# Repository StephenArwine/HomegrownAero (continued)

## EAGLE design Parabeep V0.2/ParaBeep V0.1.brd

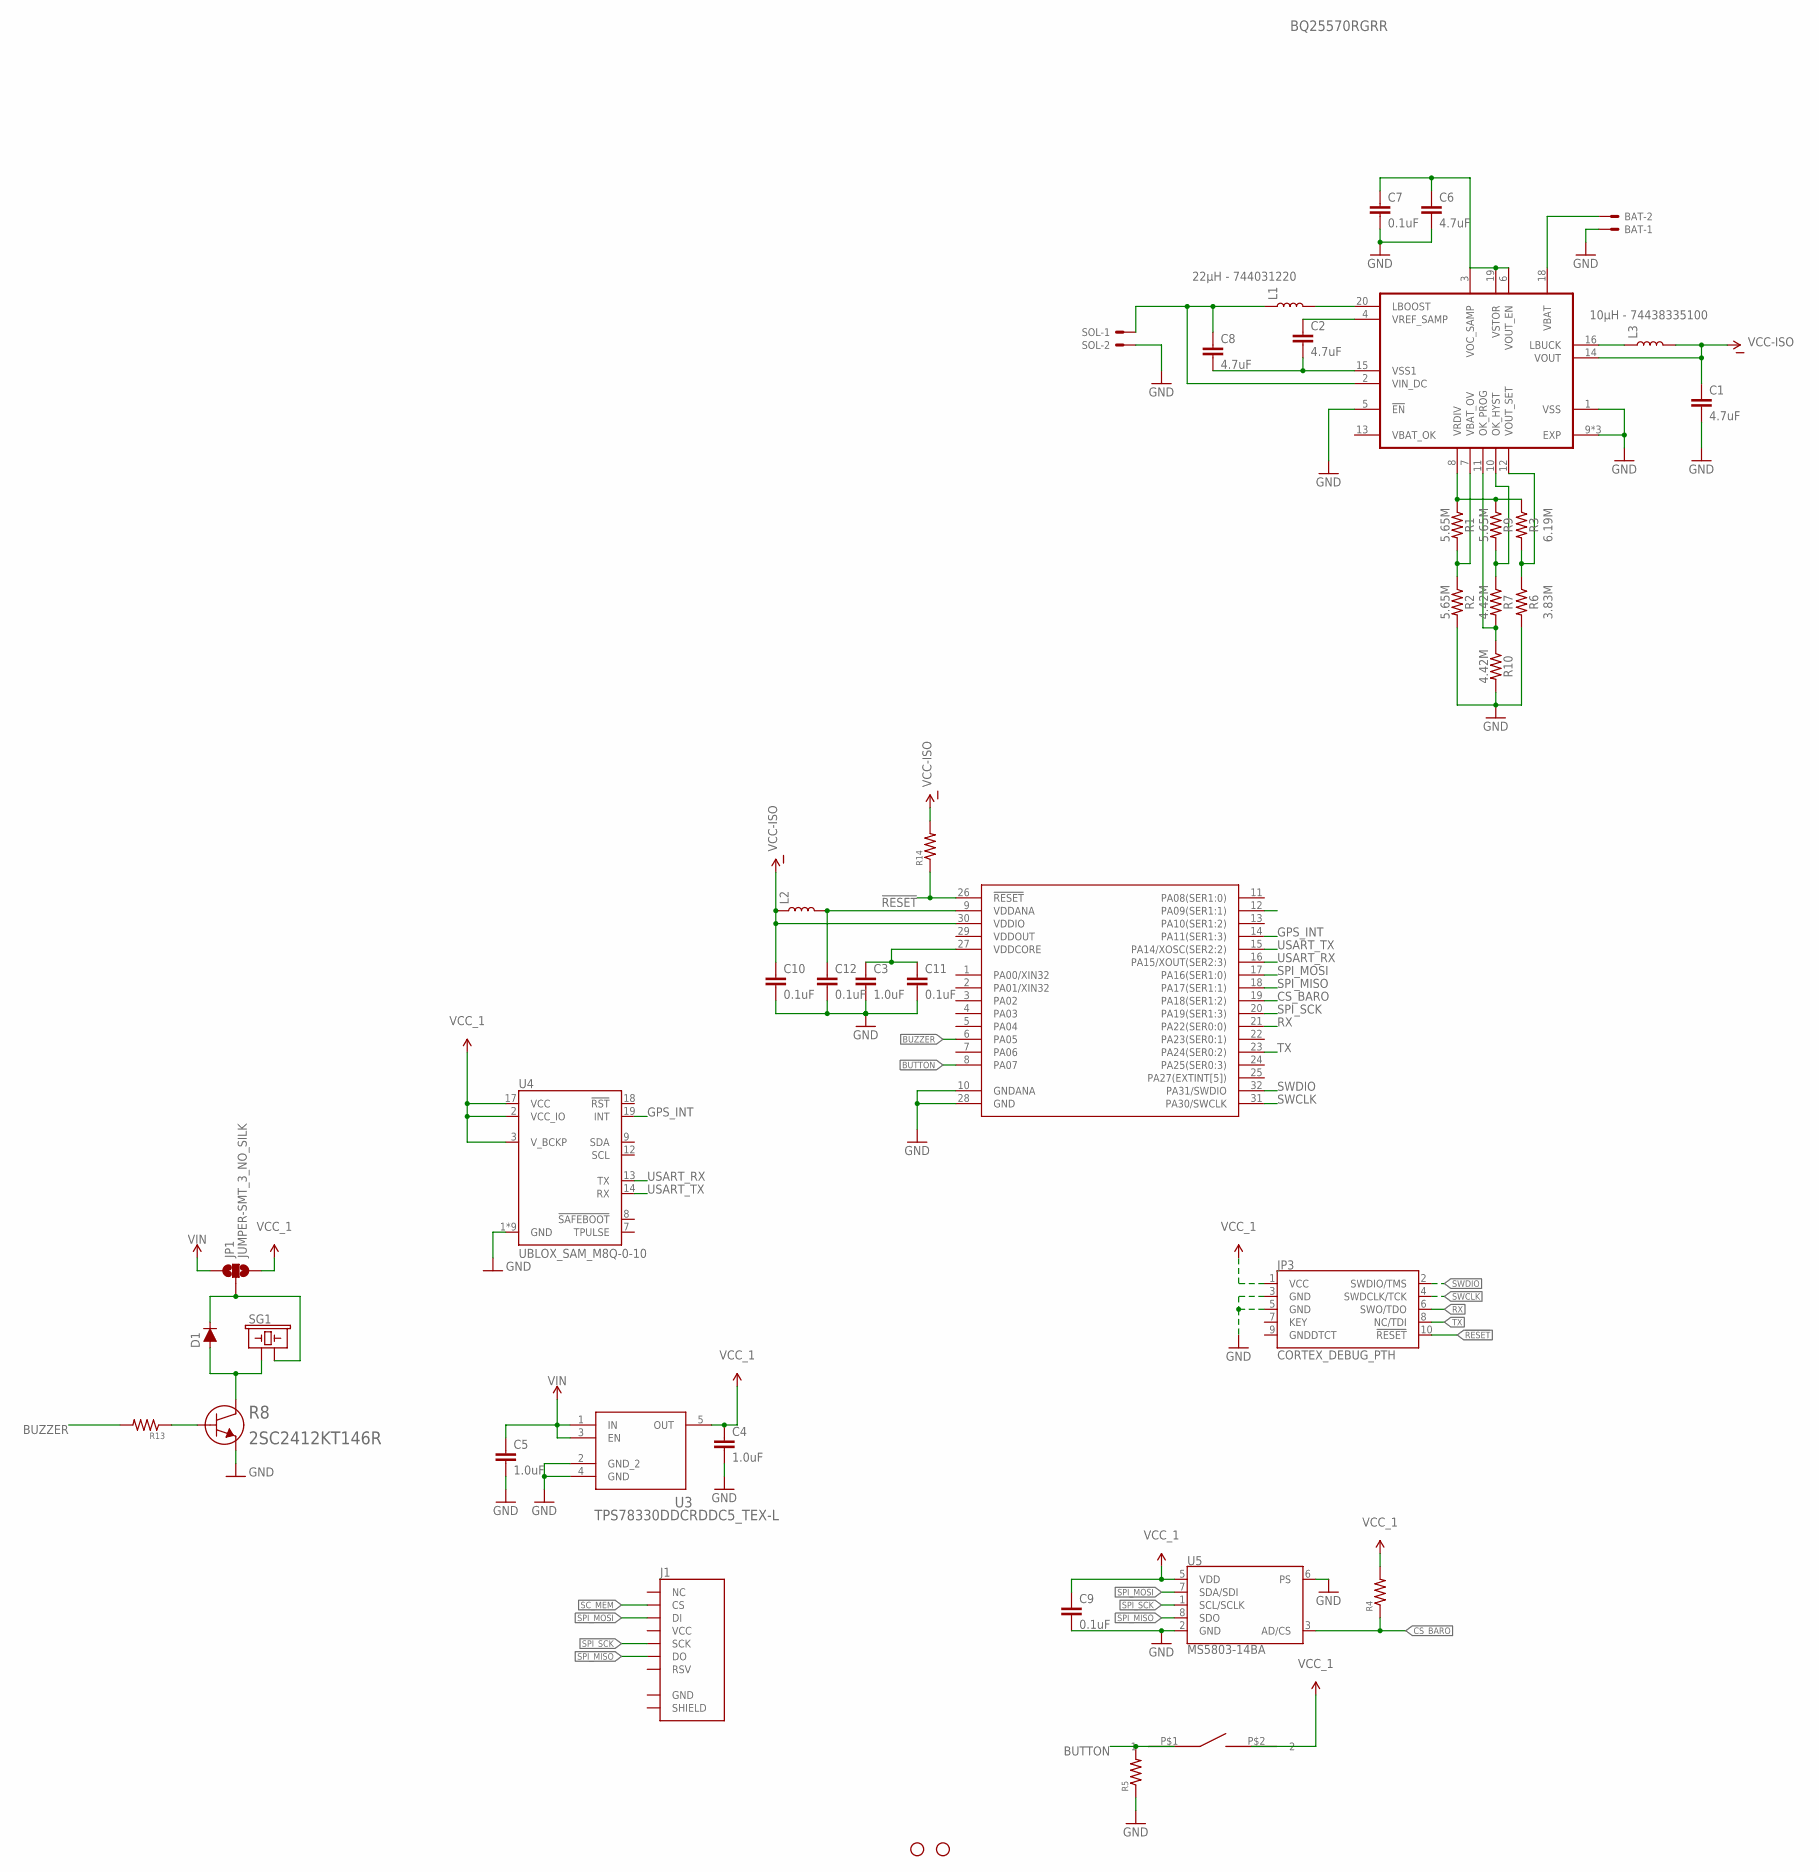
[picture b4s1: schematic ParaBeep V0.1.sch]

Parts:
BAT: SM02B-SSR-H-TB
C1, C2, C6, C8: 4.7uF; 0603
C3, C4, C5: 1.0uF; 0603
C7, C9, C10, C11, C12: 0.1uF; 0603
D1: 250mA/100V; SOD-323
H1, H2: STAND-OFFTIGHT; STAND-OFF-TIGHT
J1: MICRO-SD_CARD_SOCKETPUSH-PUSH; MICRO-SD-SOCKET
JP1: JUMPER-SMT_3_NO_SILK; SMT-JUMPER_3_NO_SILK
JP3: CORTEX_DEBUG_PTH; 2X5-PTH-1.27MM
L1: 22µH - 744031220; INDUCTOR_4.7UH
L2: INDUCTORFB-30OHM; 0603
L3: 10µH - 74438335100; INDUCTOR_4.7UH
R1, R2, R9: 5.65M; 0603
R3: 6.19M; 0603
R4, R5, R13, R14: 0402
R6: 3.83M; 0603
R7, R10: 4.42M; 0603
R8: 2SC2412KT146R; TRANS_2SB852K_ROM
SG1: BUZZER-SMD_KIT; BUZZER-CCV-KIT
SOL: SM02B-SSR-H-TB
U2: BQ25570RGRR; QFN50P350X350X100-21N
U3: TPS78330DDCRDDC5_TEX-L; DDC5_TEX-L
U4: UBLOX_SAM_M8Q-0-10; SAM-M8Q
U5: MS5803-14BA; MS5803
U6: ATSAML10E16A-AFTTQFP32_MC_MCH-L; TQFP32_MC_MCH-L
U$3: AB11AH-HC

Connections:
!RESET: JP3.10 (!RESET), R14.1, U6.26 (!RESET)
BUTTON: R5.2, U6.8 (PA07), U$3.P$1 (1)
BUZZER: R13.2, U6.6 (PA05)
CS_BARO: R4.1, U5.3 (AD/CS), U6.19 (PA18(SER1:2))
GND: BAT.1, C1.2, C3.2, C4.2, C5.2, C6.2, C7.2, C9.2, C10.2, C11.2, C12.2, JP3.3 (GND), JP3.5 (GND), R2.2, R5.1, R6.2, R8.3 (EMITTER), R10.2, SOL.2, U2.1 (VSS), U2.5 (!EN), U2.9 (EXP), U2.17 (EXP), U2.21 (EXP), U3.2 (GND_2), U3.4 (GND), U4.1 (GND), U4.4 (GND), U4.5 (GND), U4.6 (GND), U4.10 (GND), U4.11 (GND), U4.15 (GND), U4.16 (GND), U4.20 (GND), U5.2 (GND), U5.6 (PS), U6.10 (GNDANA), U6.28 (GND)
GPS_INT: U4.19 (INT), U6.14 (PA11(SER1:3))
unnamed: C3.1, C11.1, U6.27 (VDDCORE)
unnamed: D1.C, JP1.2, SG1.- (2)
unnamed: R1.1, R3.1, R9.1, U2.8 (VRDIV)
unnamed: C2.1, U2.4 (VREF_SAMP)
unnamed: R7.2, R10.1, U2.11 (OK_PROG)
unnamed: R3.2, R6.1, U2.12 (VOUT_SET)
unnamed: R7.1, R9.2, U2.10 (OK_HYST)
unnamed: R1.2, R2.1, U2.7 (VBAT_OV)
unnamed: C2.2, C8.2, U2.15 (VSS1)
unnamed: D1.A, R8.1 (COLLECTOR), SG1.+ (1)
unnamed: C8.1, L1.P$1 (1), SOL.1, U2.2 (VIN_DC)
unnamed: L3.P$1 (1), U2.16 (LBUCK)
unnamed: R8.2 (BASE), R13.1
unnamed: L1.P$2 (2), U2.20 (LBOOST)
unnamed: C6.1, C7.1, U2.3 (VOC_SAMP), U2.6 (VOUT_EN), U2.19 (VSTOR)
unnamed: C12.1, L2.2, U6.9 (VDDANA)
unnamed: BAT.2, U2.18 (VBAT)
RX: JP3.6 (SWO/TDO), U6.21 (PA22(SER0:0))
SC_MEM: J1.CS
SPI_MISO: J1.DO, U5.8 (SDO), U6.18 (PA17(SER1:1))
SPI_MOSI: J1.DI, U5.7 (SDA/SDI), U6.17 (PA16(SER1:0))
SPI_SCK: J1.SCLK (SCK), U5.1 (SCL/SCLK), U6.20 (PA19(SER1:3))
SWCLK: JP3.4 (SWDCLK/TCK), U6.31 (PA30/SWCLK)
SWDIO: JP3.2 (SWDIO/TMS), U6.32 (PA31/SWDIO)
TX: JP3.8 (NC/TDI), U6.23 (PA24(SER0:2))
USART_RX: U4.13 (TX), U6.16 (PA15/XOUT(SER2:3))
USART_TX: U4.14 (RX), U6.15 (PA14/XOSC(SER2:2))
VCC-ISO: C1.1, C10.1, L2.1, L3.P$2 (2), R14.2, U2.14 (VOUT), U6.30 (VDDIO)
VCC_1: C4.1, C9.1, JP1.3, JP3.1 (VCC), R4.2, U3.5 (OUT), U4.2 (VCC_IO), U4.3 (V_BCKP), U4.17 (VCC), U5.5 (VDD), U$3.P$2 (2)
VIN: C5.1, JP1.1, U3.1 (IN), U3.3 (EN)

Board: 2 copper layers, 42 parts (35 on the bottom side), 35 nets, no tracks yet.

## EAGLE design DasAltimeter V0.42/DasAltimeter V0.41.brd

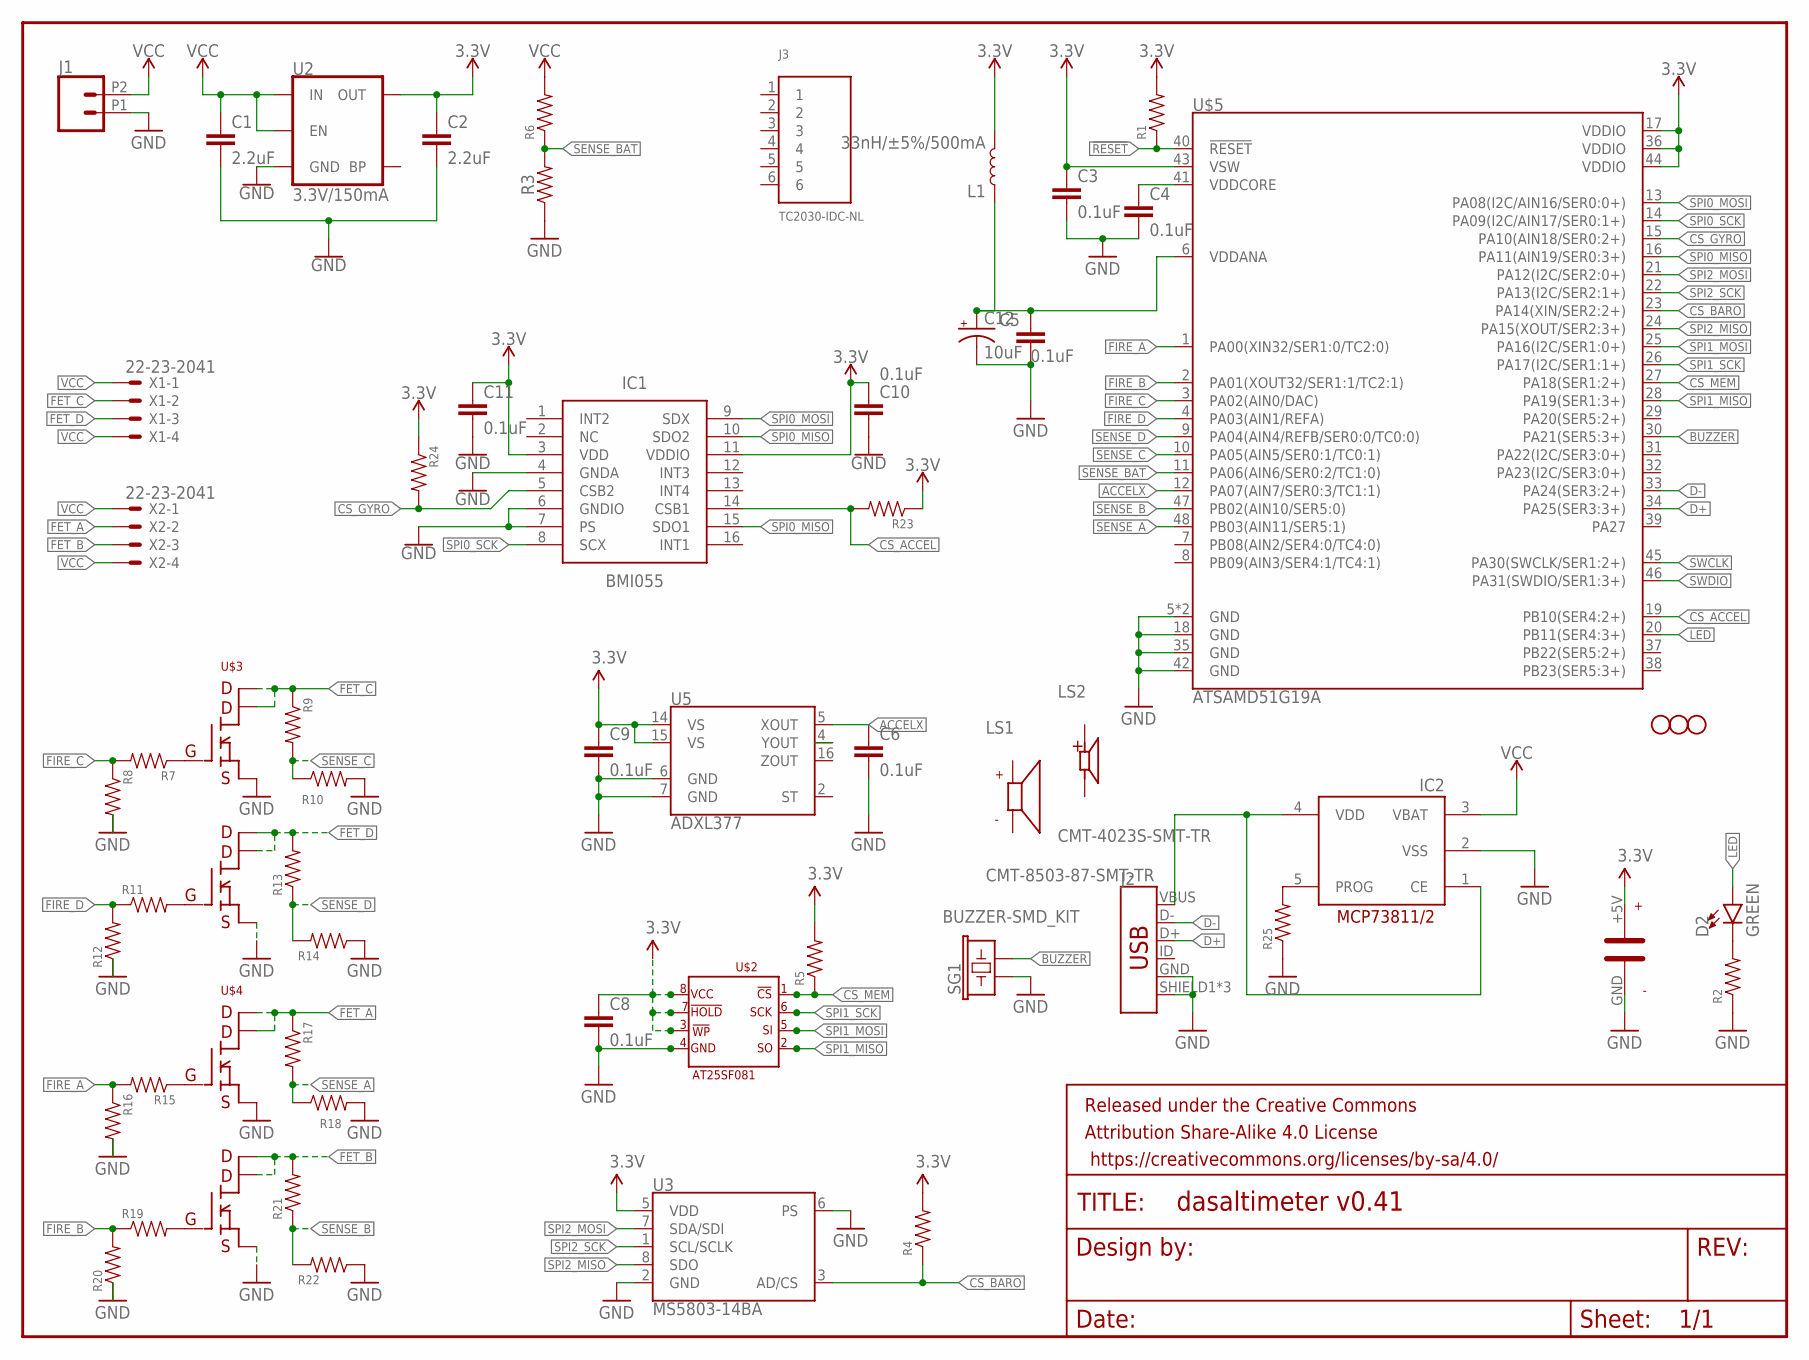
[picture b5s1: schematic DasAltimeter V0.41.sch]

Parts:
C1, C2: 2.2uF; 0603
C3, C4, C5, C6, C8, C9, C10, C11: 0.1uF; 0402
C12: 10uF; 0603-POLAR
D2: GREEN; LED-1206
FRAME1: FRAME-LETTERNO_PACKAGE; DUMMY
H1, H2, H3: STAND-OFFTIGHT; STAND-OFF-TIGHT
IC1: BMI055
IC2: MCP73811/2; SOT23-5L
J1: CONN_022.54MM_SCREWTERM; 1X02_2.54_SCREWTERM
J2: USB_MICRO-BREDUCED_PASTE; USB-B-MICRO-SMD_RED_PASTE
J3: TC2030-IDC-NL; TAG_TC2030-IDC-NL
L1: 33nH/±5%/500mA; 0603
LS1: CMT-8503-87-SMT-TR; XDCR_CMT-8503-87-SMT-TR
LS2: CMT-4023S-SMT-TR; CUI_CMT-4023S-SMT-TR
R1, R2, R3, R4, R5, R6, R7, R8, R9, R10, R11, R12, R13, R14, R15, R16, R17, R18, R19, R20, R21, R22, R23, R24, R25: 0402
SG1: BUZZER-SMD_KIT; BUZZER-CCV-KIT
U2: 3.3V/150mA; SOT23-5
U3: MS5803-14BA; MS5803
U5: ADXL377; LFCSP-16-3X3
U$1: PB-5R0H104-R
U$2: AT25SF081
U$3, U$4: SI7232DN
U$5: ATSAMD51G19A; QFN-48
X1, X2: 22-23-2041

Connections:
3.3V: C2.1, C3.1, C8.1, C9.1, C10.1, C11.1, IC1.3 (VDD), IC1.11 (VDDIO), L1.2, R1.2, R4.2, R5.2, R23.1, R24.1, U2.5 (OUT), U3.5 (VDD), U5.14 (VS), U5.15 (VS), U$1.+5V, U$2.!HOLD, U$2.!WP, U$2.VCC, U$5.17 (VDDIO), U$5.36 (VDDIO), U$5.43 (VSW), U$5.44 (VDDIO)
!RESET: R1.1, U$5.40 (!RESET!)
ACCELX: C6.1, U5.5 (XOUT), U$5.12 (PA07(AIN7/SER0:3/TC1:1))
BUZZER: SG1.- (2), U$5.30 (PA21(SER5:3+))
CS_ACCEL: IC1.14 (CSB1), R23.2, U$5.19 (PB10(SER4:2+))
CS_BARO: R4.1, U3.3 (AD/CS), U$5.23 (PA14(XIN/SER2:2+))
CS_GYRO: IC1.5 (CSB2), R24.2, U$5.15 (PA10(AIN18/SER0:2+))
CS_MEM: R5.1, U$2.!CS, U$5.27 (PA18(SER1:2+))
D+: J2.D+, U$5.34 (PA25(SER3:3+))
D-: J2.D-, U$5.33 (PA24(SER3:2+))
FET_A: R17.1, U$4.7 (PIN7), U$4.8 (PIN8), U$4.9 (PIN8), X2.2
FET_B: R21.2, U$4.5 (PIN5), U$4.6 (PIN6), U$4.10 (PIN5), X2.3
FET_C: R9.1, U$3.7 (PIN7), U$3.8 (PIN8), U$3.9 (PIN8), X1.2
FET_D: R13.2, U$3.5 (PIN5), U$3.6 (PIN6), U$3.10 (PIN5), X1.3
FIRE_A: R15.2, R16.1, U$5.1 (PA00(XIN32/SER1:0/TC2:0))
FIRE_B: R19.1, R20.2, U$5.2 (PA01(XOUT32/SER1:1/TC2:1))
FIRE_C: R7.2, R8.1, U$5.3 (PA02(AIN0/DAC))
FIRE_D: R11.1, R12.2, U$5.4 (PA03(AIN1/REFA))
GND: C1.2, C2.2, C3.2, C4.2, C5.2, C6.2, C8.2, C9.2, C10.2, C11.2, C12.-, IC1.4 (GNDA), IC1.6 (GNDIO), IC1.7 (PS), IC2.2 (VSS), J1.P1 (1), J2.GND, J2.SHIELD1 (SHIELD), J2.SHIELD2 (SHIELD), J2.SHIELD3 (SHIELD), R2.1, R3.1, R8.2, R10.2, R12.1, R14.1, R16.2, R18.2, R20.1, R22.1, R25.1, SG1.+ (1), U2.2 (GND), U3.2 (GND), U3.6 (PS), U5.6 (GND), U5.7 (GND), U$1.GND, U$2.GND, U$3.1 (PIN1), U$3.3 (PIN3), U$4.1 (PIN1), U$4.3 (PIN3), U$5.5 (GND), U$5.18 (GND), U$5.35 (GND), U$5.42 (GND), U$5.EP (GND)
LED: D2.A, U$5.20 (PB11(SER4:3+))
unnamed: R7.1, U$3.2 (PIN2)
unnamed: C4.1, U$5.41 (VDDCORE)
unnamed: C5.1, C12.+, L1.1, U$5.6 (VDDANA)
unnamed: IC2.1 (CE), IC2.4 (VDD), J2.VBUS
unnamed: IC2.5 (PROG), R25.2
unnamed: R11.2, U$3.4 (PIN4)
unnamed: R15.1, U$4.2 (PIN2)
unnamed: R19.2, U$4.4 (PIN4)
unnamed: D2.C, R2.2
SENSE_A: R17.2, R18.1, U$5.48 (PB03(AIN11/SER5:1))
SENSE_B: R21.1, R22.2, U$5.47 (PB02(AIN10/SER5:0))
SENSE_BAT: R3.2, R6.1, U$5.11 (PA06(AIN6/SER0:2/TC1:0))
SENSE_C: R9.2, R10.1, U$5.10 (PA05(AIN5/SER0:1/TC0:1))
SENSE_D: R13.1, R14.2, U$5.9 (PA04(AIN4/REFB/SER0:0/TC0:0))
SPI0_MISO: IC1.10 (SDO2), IC1.15 (SDO1), U$5.16 (PA11(AIN19/SER0:3+))
SPI0_MOSI: IC1.9 (SDX), U$5.13 (PA08(I2C/AIN16/SER0:0+))
SPI0_SCK: IC1.8 (SCX), U$5.14 (PA09(I2C/AIN17/SER0:1+))
SPI1_MISO: U$2.SO, U$5.28 (PA19(SER1:3+))
SPI1_MOSI: U$2.SI, U$5.25 (PA16(I2C/SER1:0+))
SPI1_SCK: U$2.SCK, U$5.26 (PA17(I2C/SER1:1+))
SPI2_MISO: U3.8 (SDO), U$5.24 (PA15(XOUT/SER2:3+))
SPI2_MOSI: U3.7 (SDA/SDI), U$5.21 (PA12(I2C/SER2:0+))
SPI2_SCK: U3.1 (SCL/SCLK), U$5.22 (PA13(I2C/SER2:1+))
SWCLK: U$5.45 (PA30(SWCLK/SER1:2+))
SWDIO: U$5.46 (PA31(SWDIO/SER1:3+))
VCC: C1.1, IC2.3 (VBAT), J1.P2 (2), R6.2, U2.1 (IN), U2.3 (EN), X1.1, X1.4, X2.1, X2.4

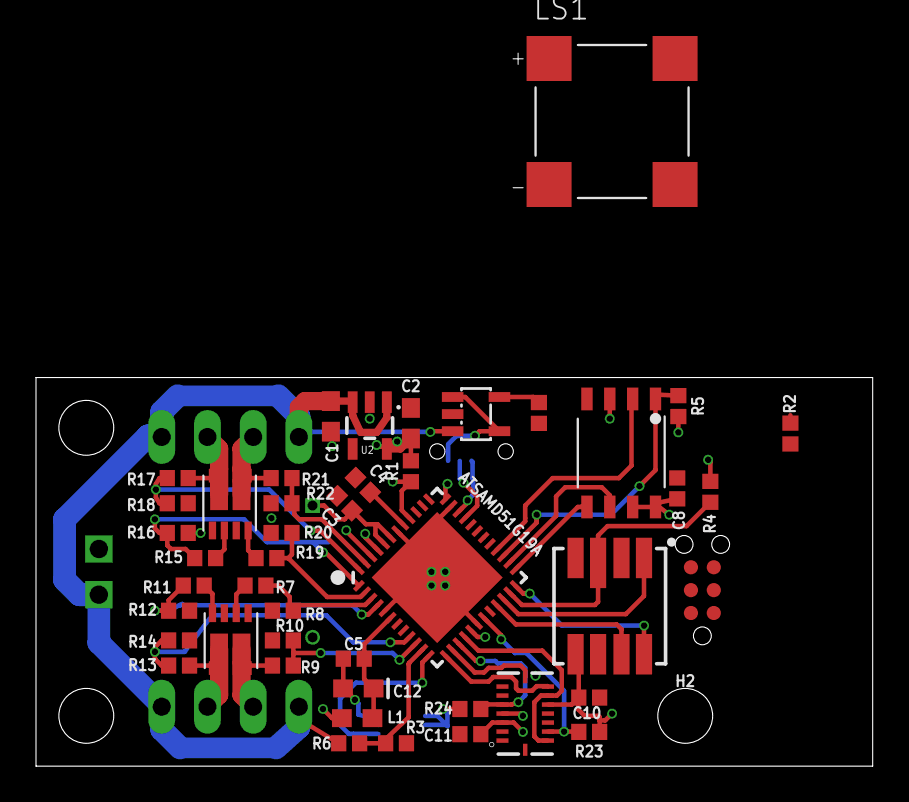
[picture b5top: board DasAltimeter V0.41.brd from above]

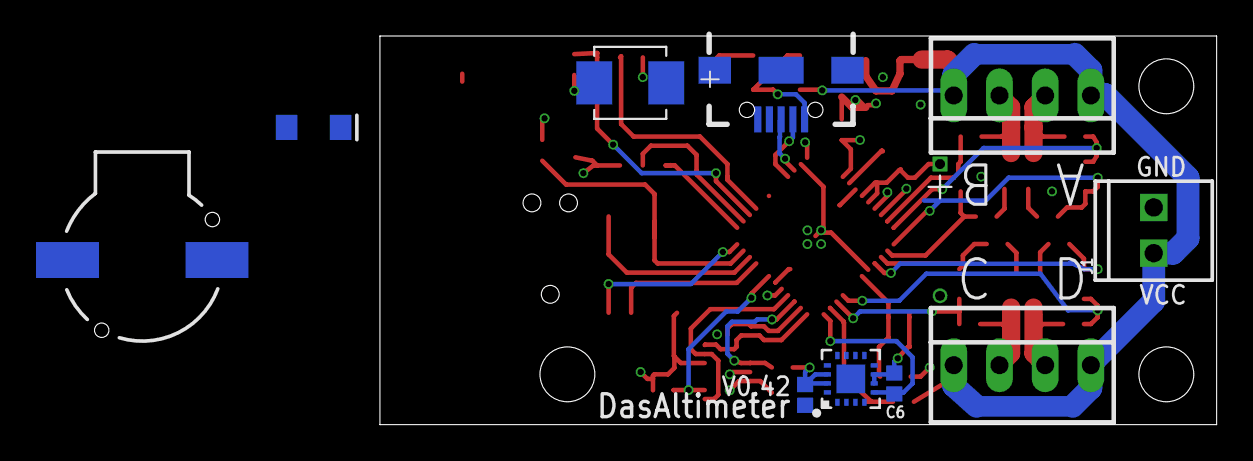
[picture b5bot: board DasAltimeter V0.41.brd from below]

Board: 4 copper layers, 46.5 x 21.6 mm, 60 parts (11 on the bottom side), 44 nets.

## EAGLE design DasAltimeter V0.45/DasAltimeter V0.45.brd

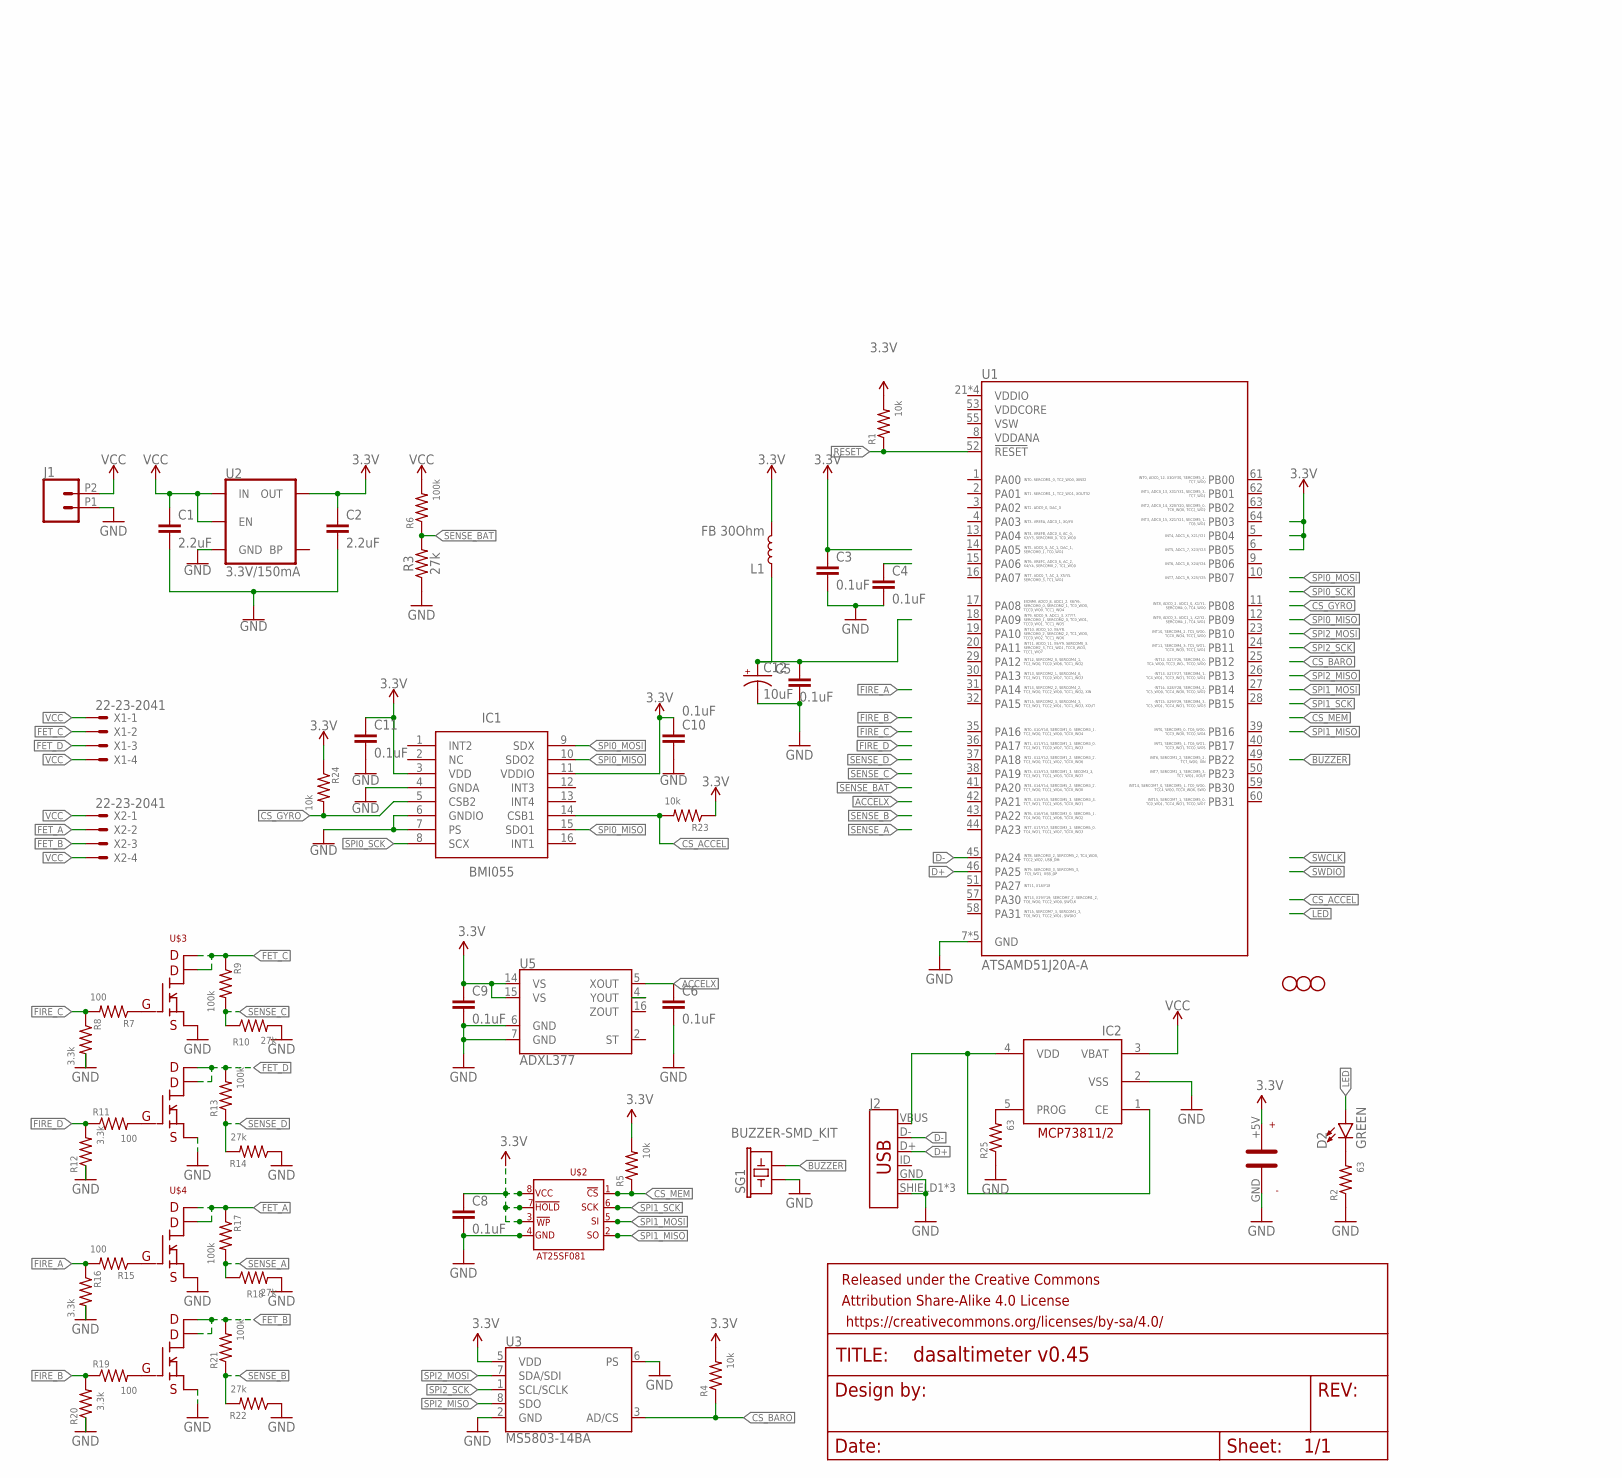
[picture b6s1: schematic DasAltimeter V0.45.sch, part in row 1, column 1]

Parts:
C1, C2: 2.2uF; 0603
C3, C4, C5, C6, C8, C9, C10, C11: 0.1uF; 0402
C12: 10uF; 0603-POLAR
D2: GREEN; LED-1206
FRAME1: FRAME-LETTERNO_PACKAGE; DUMMY
H1, H2, H3: STAND-OFFTIGHT; STAND-OFF-TIGHT
IC1: BMI055
IC2: MCP73811/2; SOT23-5L
J1: CONN_022.54MM_SCREWTERM; 1X02_2.54_SCREWTERM
J2: USB_MICRO-BREDUCED_PASTE; USB-B-MICRO-SMD_RED_PASTE
L1: FB 30Ohm; 0603
R1, R4, R5, R23, R24: 10k; 0402
R2, R25: 63; 0402
R3, R10, R14, R18, R22: 27k; 0402
R6, R9, R13, R17, R21: 100k; 0402
R7, R11, R15, R19: 100; 0402
R8, R12, R16, R20: 3.3k; 0402
SG1: BUZZER-SMD_KIT; BUZZER-CCV-KIT
U1: ATSAMD51J20A-A; TQFP64
U2: 3.3V/150mA; SOT23-5
U3: MS5803-14BA; MS5803
U5: ADXL377; LFCSP-16-3X3
U$1: PB-5R0H104-R
U$2: AT25SF081
U$3, U$4: SI7232DN
X1, X2: 22-23-2041

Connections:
3.3V: C2.1, C3.1, C8.1, C9.1, C10.1, C11.1, IC1.3 (VDD), IC1.11 (VDDIO), L1.2, R1.2, R4.2, R5.2, R23.1, R24.1, U2.5 (OUT), U3.5 (VDD), U5.14 (VS), U5.15 (VS), U$1.+5V, U$2.!HOLD, U$2.!WP, U$2.VCC
!RESET: R1.1, U1.52 (!RESET)
ACCELX: C6.1, U5.5 (XOUT)
BUZZER: SG1.- (2)
CS_ACCEL: IC1.14 (CSB1), R23.2
CS_BARO: R4.1, U3.3 (AD/CS)
CS_GYRO: IC1.5 (CSB2), R24.2
CS_MEM: R5.1, U$2.!CS
D+: J2.D+, U1.46 (PA25)
D-: J2.D-, U1.45 (PA24)
FET_A: R17.1, U$4.7 (PIN7), U$4.8 (PIN8), U$4.9 (PIN8), X2.2
FET_B: R21.2, U$4.5 (PIN5), U$4.6 (PIN6), U$4.10 (PIN5), X2.3
FET_C: R9.1, U$3.7 (PIN7), U$3.8 (PIN8), U$3.9 (PIN8), X1.2
FET_D: R13.2, U$3.5 (PIN5), U$3.6 (PIN6), U$3.10 (PIN5), X1.3
FIRE_A: R15.2, R16.1
FIRE_B: R19.1, R20.2
FIRE_C: R7.2, R8.1
FIRE_D: R11.1, R12.2
GND: C1.2, C2.2, C3.2, C4.2, C5.2, C6.2, C8.2, C9.2, C10.2, C11.2, C12.-, IC1.4 (GNDA), IC1.6 (GNDIO), IC1.7 (PS), IC2.2 (VSS), J1.P1 (1), J2.GND, J2.SHIELD1 (SHIELD), J2.SHIELD2 (SHIELD), J2.SHIELD3 (SHIELD), R2.1, R3.1, R8.2, R10.2, R12.1, R14.1, R16.2, R18.2, R20.1, R22.1, R25.1, SG1.+ (1), U1.7 (GND), U1.22 (GND), U1.33 (GND), U1.47 (GND), U1.54 (GND), U2.2 (GND), U3.2 (GND), U3.6 (PS), U5.6 (GND), U5.7 (GND), U$1.GND, U$2.GND, U$3.1 (PIN1), U$3.3 (PIN3), U$4.1 (PIN1), U$4.3 (PIN3)
LED: D2.A
unnamed: R7.1, U$3.2 (PIN2)
unnamed: C5.1, C12.+, L1.1
unnamed: IC2.1 (CE), IC2.4 (VDD), J2.VBUS
unnamed: IC2.5 (PROG), R25.2
unnamed: R11.2, U$3.4 (PIN4)
unnamed: R15.1, U$4.2 (PIN2)
unnamed: R19.2, U$4.4 (PIN4)
unnamed: D2.C, R2.2
SENSE_A: R17.2, R18.1
SENSE_B: R21.1, R22.2
SENSE_BAT: R3.2, R6.1
SENSE_C: R9.2, R10.1
SENSE_D: R13.1, R14.2
SPI0_MISO: IC1.10 (SDO2), IC1.15 (SDO1)
SPI0_MOSI: IC1.9 (SDX)
SPI0_SCK: IC1.8 (SCX)
SPI1_MISO: U$2.SO
SPI1_MOSI: U$2.SI
SPI1_SCK: U$2.SCK
SPI2_MISO: U3.8 (SDO)
SPI2_MOSI: U3.7 (SDA/SDI)
SPI2_SCK: U3.1 (SCL/SCLK)
VCC: C1.1, IC2.3 (VBAT), J1.P2 (2), R6.2, U2.1 (IN), U2.3 (EN), X1.1, X1.4, X2.1, X2.4

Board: 4 copper layers, 57 parts (10 on the bottom side), 33 nets, no tracks yet.

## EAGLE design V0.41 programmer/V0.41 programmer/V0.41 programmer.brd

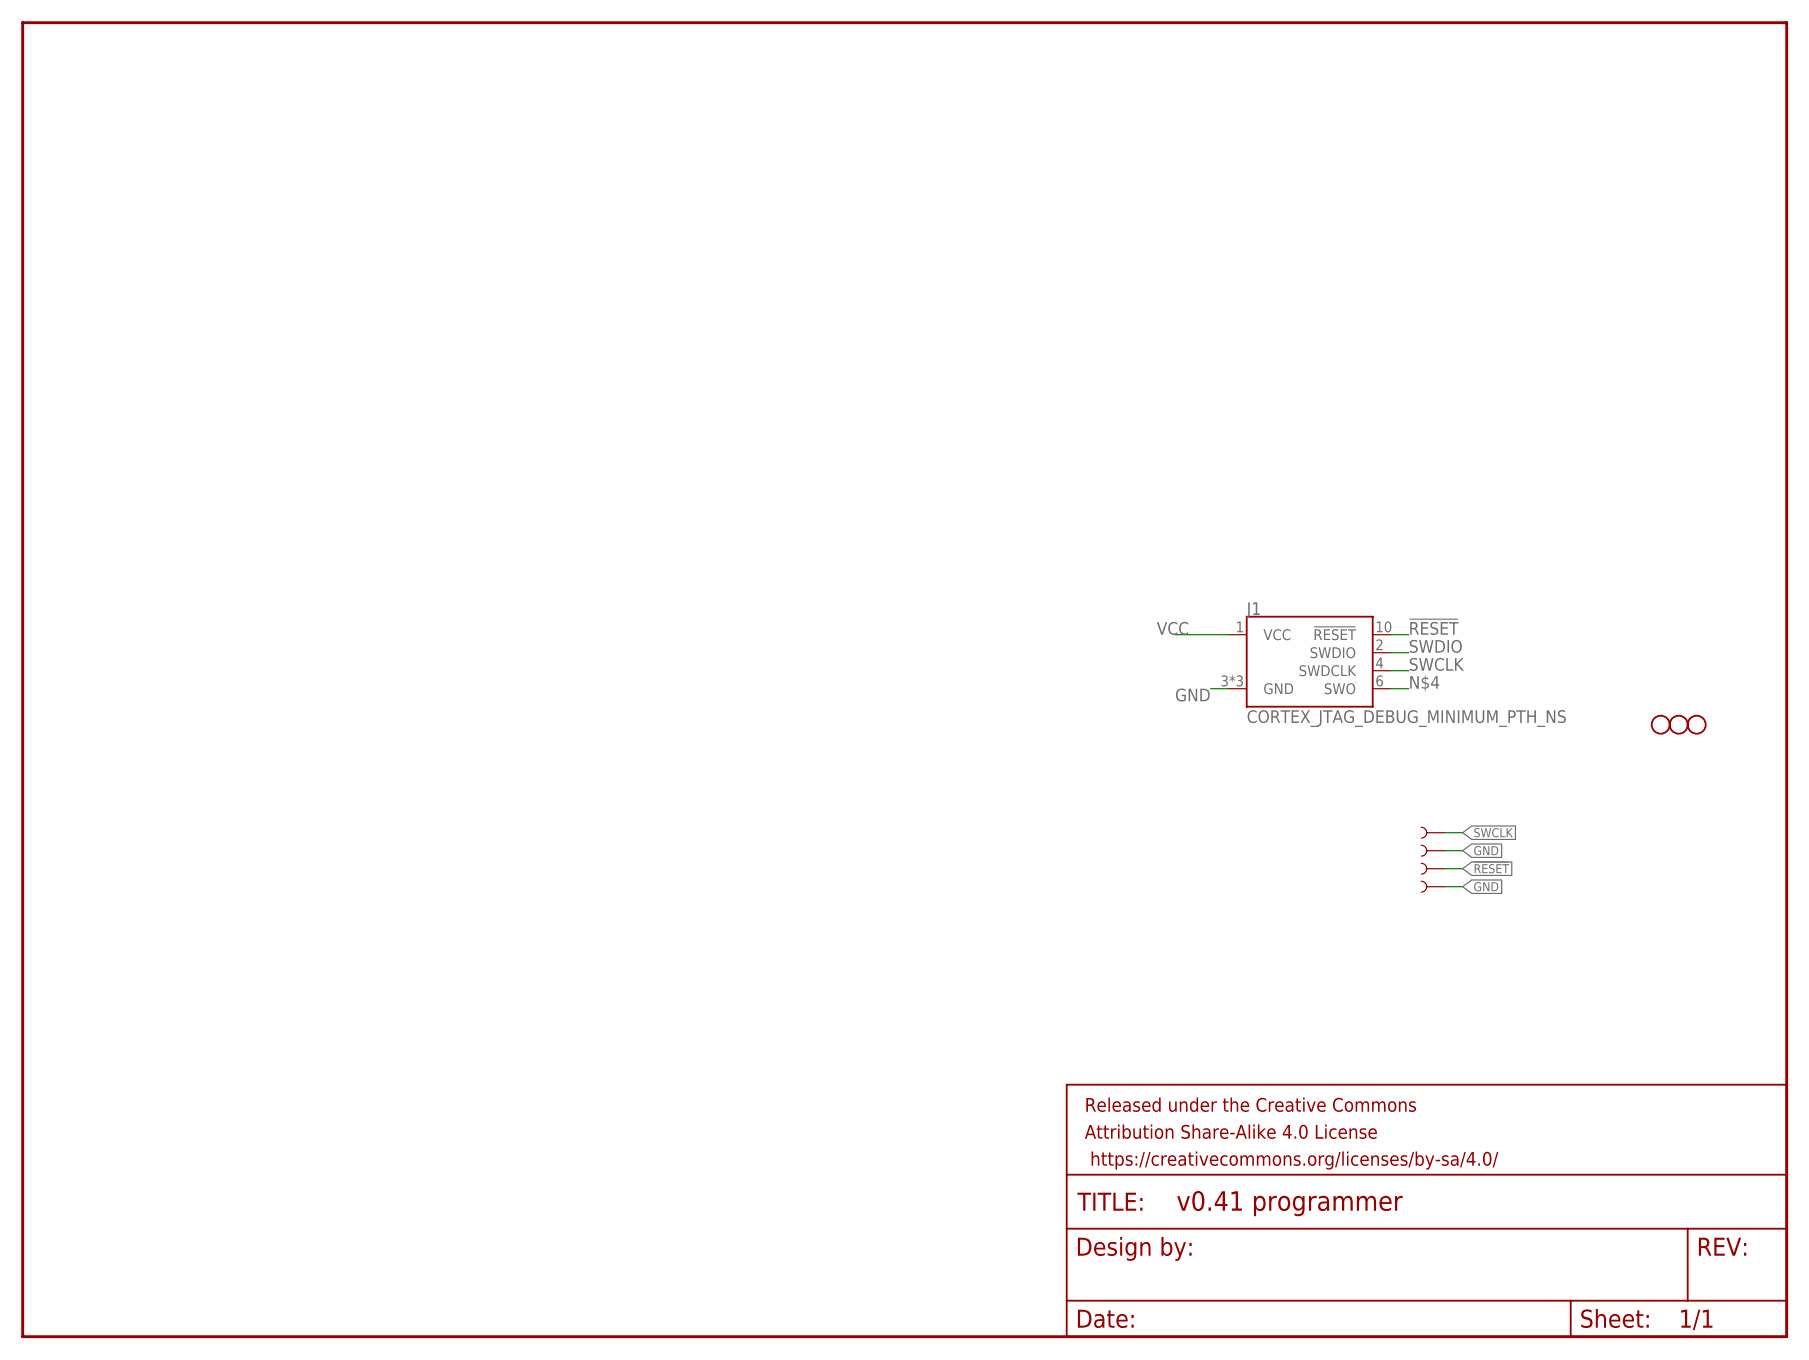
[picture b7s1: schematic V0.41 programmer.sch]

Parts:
FRAME1: FRAME-LETTERNO_PACKAGE; DUMMY
H1, H2, H3: STAND-OFFTIGHT; STAND-OFF-TIGHT
J1: CORTEX_JTAG_DEBUG_MINIMUM_PTH_NS; 2X5-PTH-1.27MM-NO_SILK
TP1, TP2, TP3, TP4: TEST-POINT3; PAD.03X.03

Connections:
!RESET: J1.10 (!RESET), TP3.P$1
GND: J1.3 (GND), J1.5 (GND), J1.9 (GND), TP2.P$1, TP4.P$1
SWCLK: J1.4 (SWDCLK), TP1.P$1
SWDIO: J1.2 (SWDIO)
VCC: J1.1 (VCC)

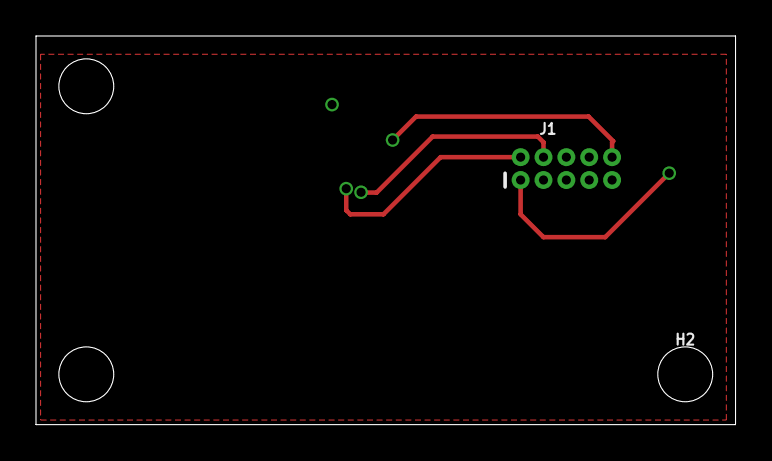
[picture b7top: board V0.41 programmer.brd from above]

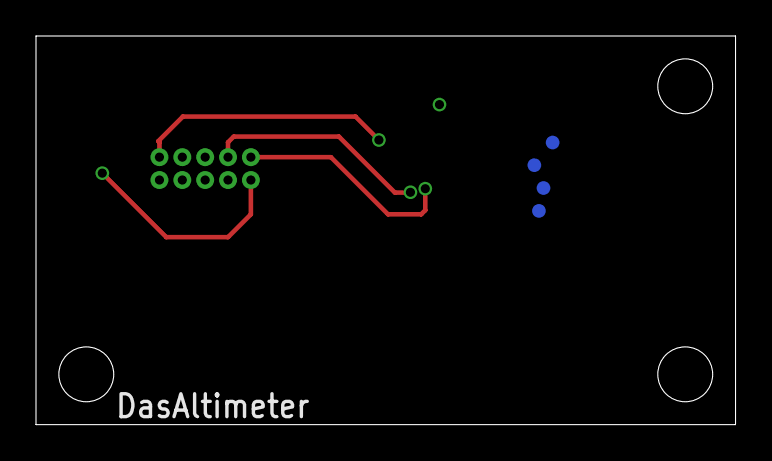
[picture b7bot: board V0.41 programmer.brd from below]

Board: 2 copper layers, 38.9 x 21.6 mm, 9 parts (4 on the bottom side), 3 nets.
